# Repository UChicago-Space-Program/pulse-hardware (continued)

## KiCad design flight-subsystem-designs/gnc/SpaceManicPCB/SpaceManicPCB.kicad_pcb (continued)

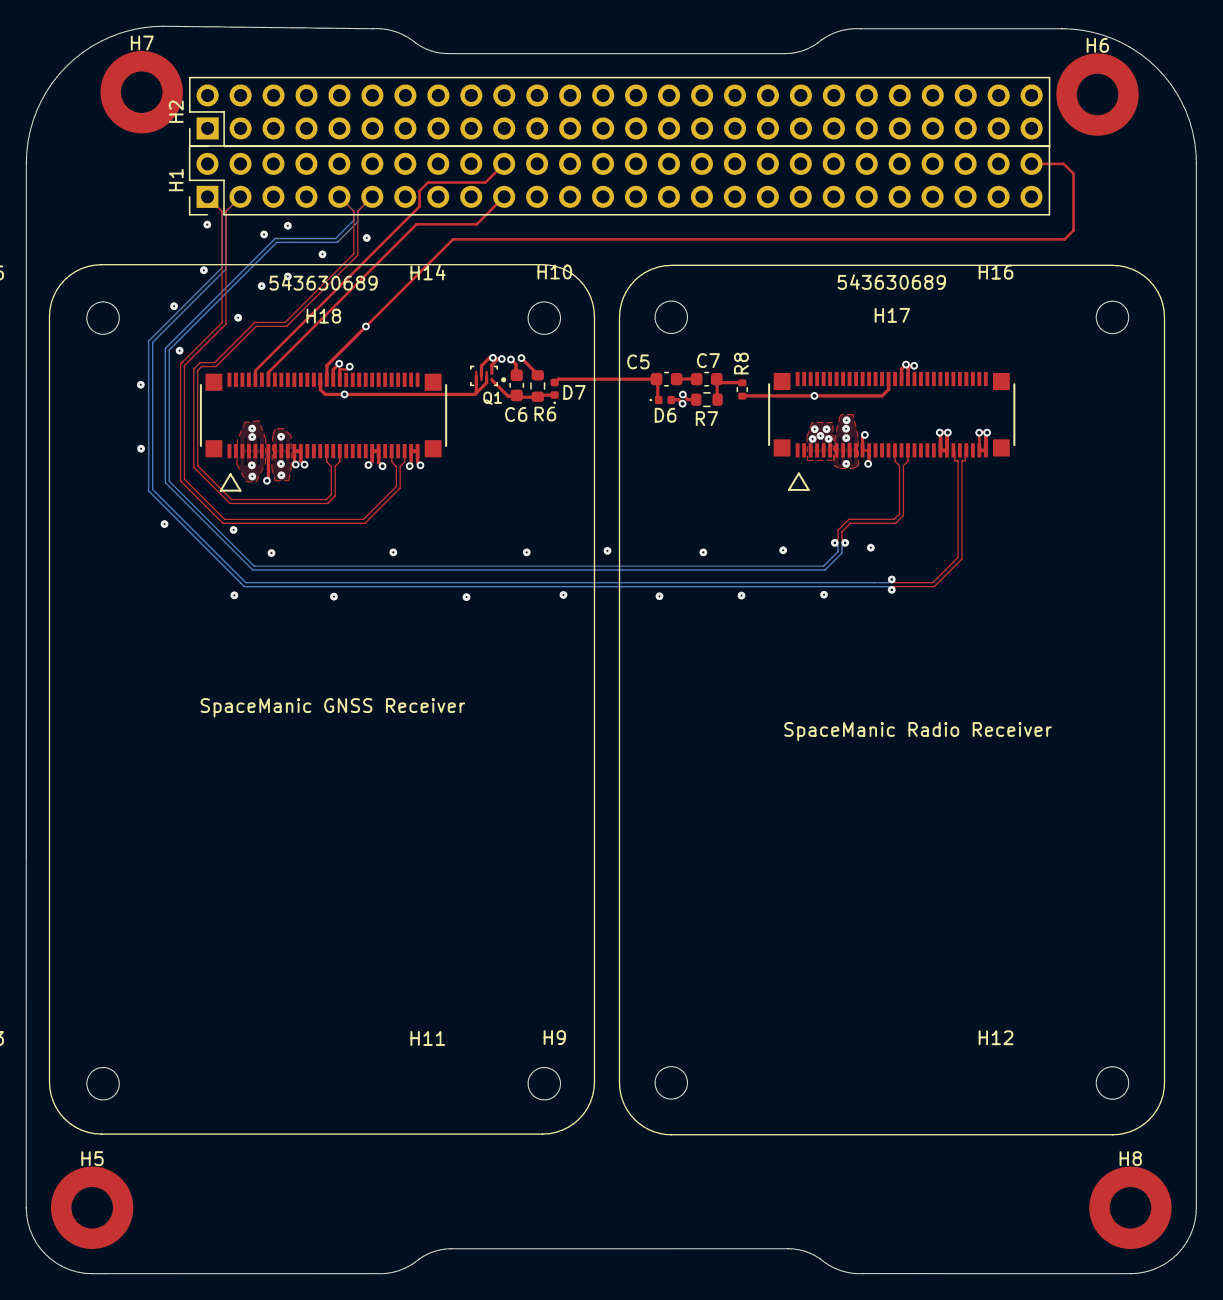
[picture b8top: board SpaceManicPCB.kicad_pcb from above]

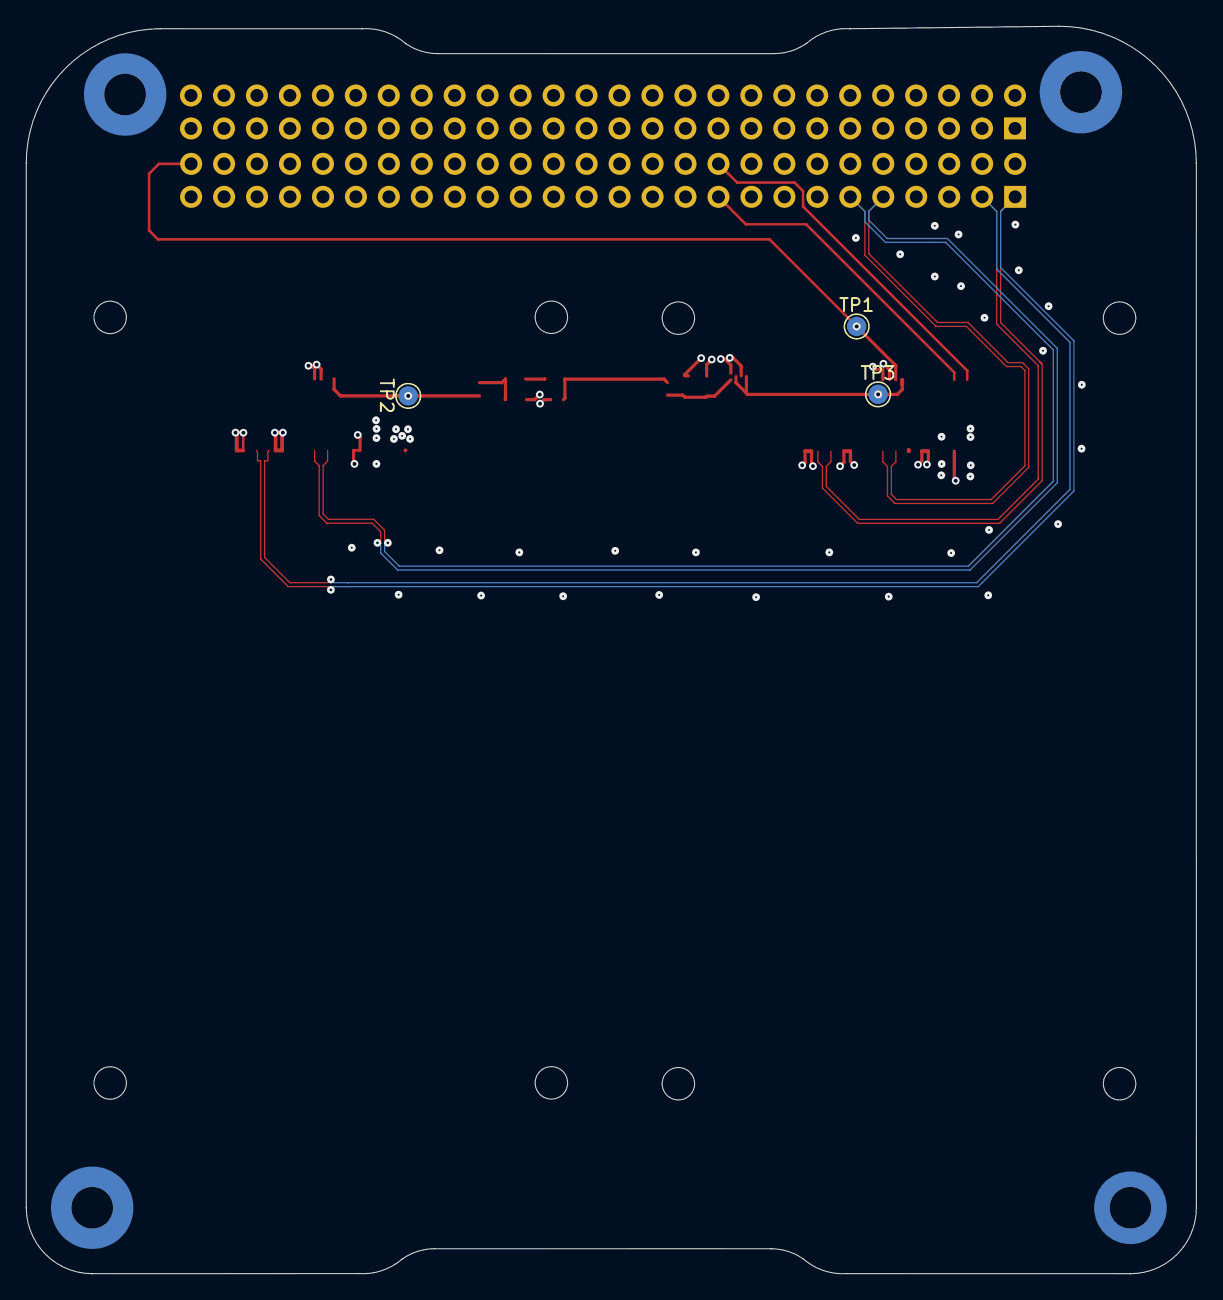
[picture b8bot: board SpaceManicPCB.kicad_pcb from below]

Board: 4 copper layers, 90.2 x 96.1 mm, 28 parts (3 on the bottom side), 16 nets.

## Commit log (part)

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2025-11-07 Revise board documentation for GPS-RadioPCB
    Updated the board documentation to provide a clearer purpose and overview of the Global Navigation and Communications Board, including features, requirements, software accompaniments, and components.
2025-11-11 Add choice justifications for Murgas and Celeste
    Added justifications for Murgas and Celeste choices, including power consumption, data rates, and performance metrics.
2025-11-16 feat: pdu 4.0 in progress
2025-11-26 Document individual parts justification for GPS Radio PCB
    Added justification for individual parts used in the GPS Radio PCB design, including resistor values and recommendations for decoupling capacitors.
2025-11-26 Update board documentation with parts justification
    Added justification for individual parts including resistor values and recommendations for decoupling capacitors.
2025-11-26 Clarify I2C pull-up resistor requirement
2025-12-04 New C=
2025-12-17 deleted old gnc files
2026-01-11 updates from old computer
2026-01-11 Chris' laser driver files
2026-01-13 payload controller
2026-01-29 For Zumi Schematik Review
2026-02-01 Update plcl schematics
2026-02-01 Update Payload Controller schematic
2026-02-01 laserdriver: new laser driver revision schematic
2026-02-02 laserdriver: add terminations and some fixups
2026-02-02 laserdriver: forgot my decouplign caps
2026-02-02 laserdriver: add ferrite beads and assign footprints
2026-02-02 laserdriver: first board revision; changed LDO
2026-02-03 Add files via upload
    Ian OBC recreation with a watchdog timer rather than a processor, and different symbols for the BeagleBone and PC104 headers
2026-02-03 laserdriver: add bnc and mounting holes
2026-02-07 fix: added ucsp schematic template
2026-02-08 Ian OBC recreation with a watchdog timer and new symbols
2026-02-08 fix: added ucsp header to obc and deleted duplicate schematic
2026-02-08 Update PC104 schematic
2026-02-08 fix: qc vee label
2026-02-08 Update PLCL schematic
2026-02-10 NAND memory removed, more GPIO used for MFP's
2026-02-10 Added grounded mounting holes
2026-02-10 corrections
2026-02-15 feat: PDU updates and laser driver v1.0.1
2026-02-15 Added overvoltage regulation, *check J8*
2026-02-17 laserdriver: add power & input isolation
2026-02-17 laserdriver: reset all annotations and cleared pcb :sob:
2026-02-17 laserdriver: well f****
2026-02-18 laserdriver: finish routing (we're so back)
2026-02-22 laserdriver: signal gnd isolation; fix drcs; ready to export!
2026-02-22 Owen Law Done with SIB.
2026-02-23 OBC Version 6.1
2026-02-23 OBC Version 6.1 - not trustworthy
2026-02-24 Hashed down to warnings - Still not trustworthy
2026-02-24 OBC Version 6.1; no warnings, no errors (pcb)
2026-02-27 DRC Friendly: Fixed Connectors
2026-03-02 Routing is fixed unless I missed something
2026-03-03 Intermediate fixes, still WIP
2026-03-05 More Patches and 5V Re-Added
2026-03-07 Mounting holes still need work
2026-03-14 Final Changes
2026-03-24 Not LibreCube Friendly, Holes Removed
2026-03-24 feat: small tweaks for schematic review
2026-03-28 Librecube Friendly Hopefully; Wiring Needs Work :C
2026-03-29 Added UART
2026-04-07 battboard: Unfinished *new* version based on PyCubed :smiley:
    Back to basics...
2026-04-14 feat: PDU 4.0.0 (WIP)
2026-04-15 feat: 3.1
2026-04-15 battboard: v4.0.0 PyCubed Edition
2026-04-19 feat improvement
2026-05-02 Updated to match current ICD on Drive
2026-05-02 PCB side of schematic update to follow ICD
2026-05-13 feat: new quadcell rev in progress
2026-05-16 misc: add gitignore
2026-05-16 ld: v1.2.0; new LDO, corrected isopower footprint, disspation res
2026-05-17 New Board Version with better Signal Integrity
2026-05-22 Hopefully Final-ish Board
2026-05-24 Final Board (Hopefully)
2026-05-24 where are my gerbers
2026-06-02 It should be good this time guys trust
2026-06-11 obc changes'
2026-06-23 Fixed UART
2026-06-24 New Footprint Fixes and Routing Improvements
